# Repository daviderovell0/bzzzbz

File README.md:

**bzzzbz** is a video synthesizer that dynamically reacts to an audio input to create images and visuals that can be manipulated for integrated audio-visual performances.  <br>
This product is meant to be a simpler and cheaper alternative to commercial analog video synthesizers, still providing a flexible interface to enhance musical expression.

If you are a musician, a visual artist or are curious about the mesmerizing videos on the wall of your local techno club, build and use  **bzzzbz** to experiment and play with audio-reactive visuals! Among its main features, this open-source video synth gives you the live control of video parameters and the possibility of creating your own mappings and patterns for immersive audiovisual performances.
## Documentation
Visit our [wiki](https://github.com/daviderovell0/bzzzbz/wiki) for the full documentation. 
## Contributions
- Davide Rovelli (daviderovell0)
- Peter Nagy (deetrone)
- Marcell Illyes (marcellillyes)

This project was born at the University of Glasgow, School of Engineering. Credits to Dr.Bernd Porr, Dr. Nicholas Bailey and their Real Time Embedded Programming course.

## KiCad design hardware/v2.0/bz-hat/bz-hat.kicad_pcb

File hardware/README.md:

# Hardware
This folder contains information, documents and design files for the *bzzzbz* digital video synth hardware.

### Tools
PCBs were designed using KiCAD 5.15.

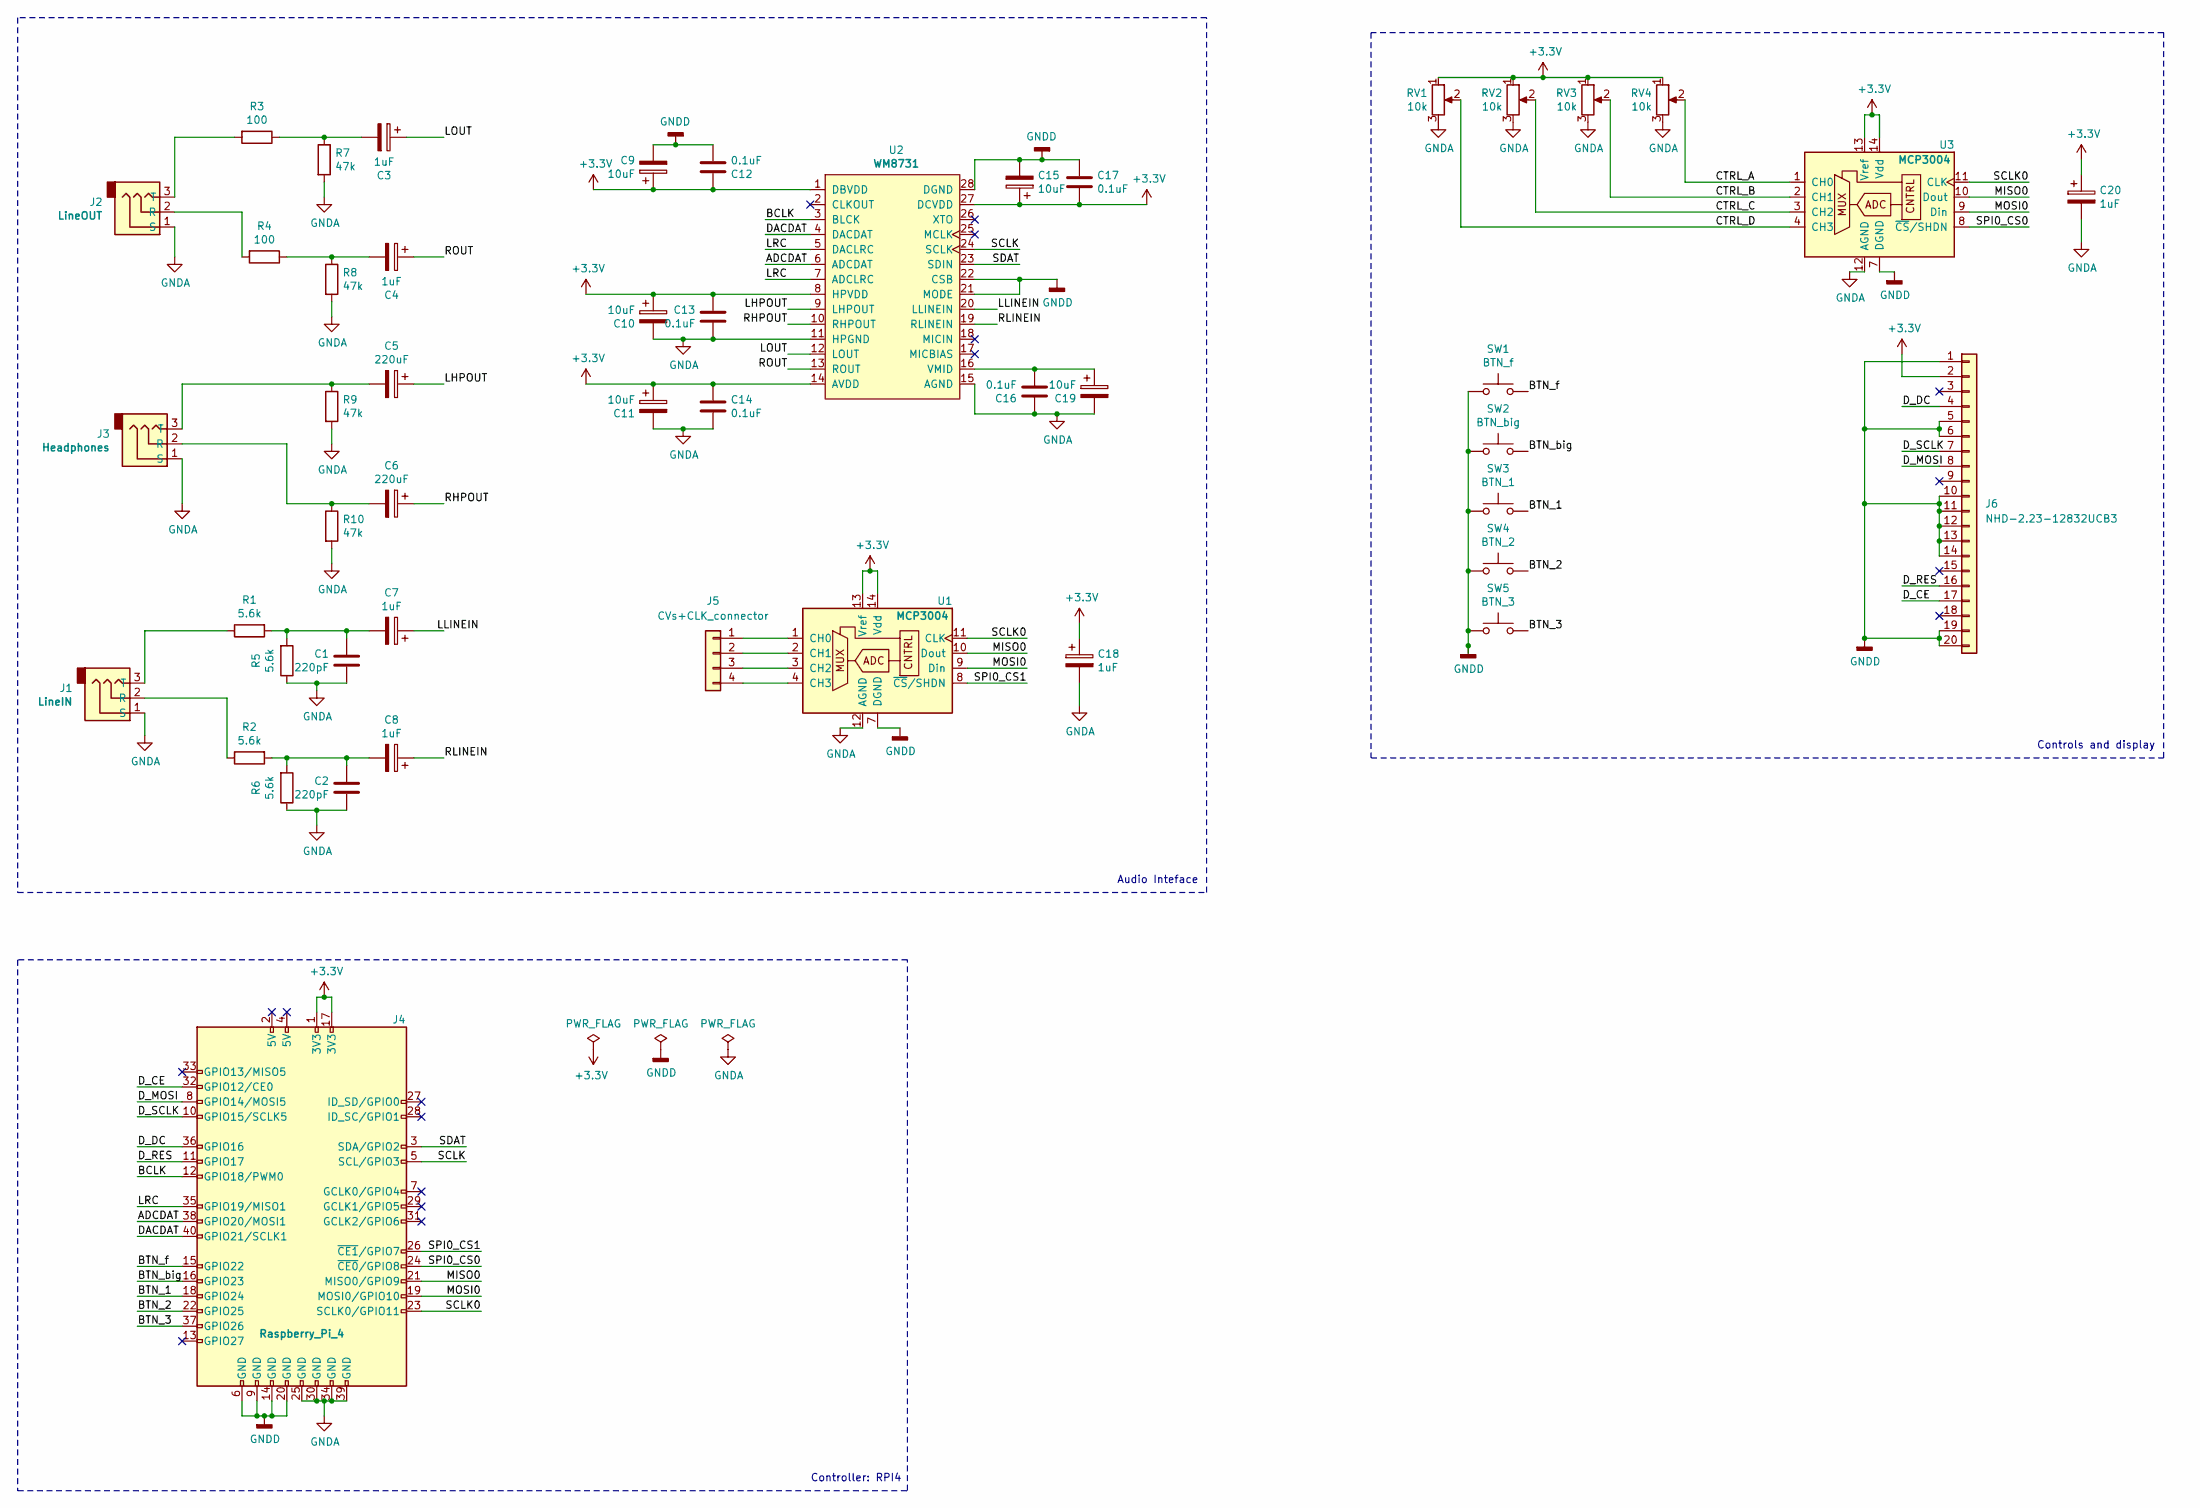
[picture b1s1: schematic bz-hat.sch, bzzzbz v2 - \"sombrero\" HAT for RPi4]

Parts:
C1, C2: 220pF; C_0603_1608Metric; Manufacturer part # CL10B221KB8NNNC; LCSC C1603
C3, C4, C7, C8, C18, C20: 1uF; CP_EIA-3216-18_Kemet-A; Manufacturer part # TAJA105K035RNJ; LCSC C7176
C5, C6: 220uF; CP_Elec_6.3x7.7; Manufacturer part # VES221M1CTR-0607; LCSC C127327
C9, C10, C11, C15, C19: 10uF; CP_EIA-3216-18_Kemet-A; Manufacturer part # TAJA106K016RNJ; LCSC C7171
C12, C14, C16, C17: 0.1uF; C_0603_1608Metric; Manufacturer part # CC0603KRX7R9BB104; LCSC C14663
C13: 0.1uF; C_1206_3216Metric; Manufacturer part # CL31B104KBCNNNC; LCSC C24497
J1: LineIN; Jack_3.5mm_CUI_SJ1-3533NG_Horizontal; Manufacturer part # SJ1-3533NG
J2: LineOUT; Jack_3.5mm_CUI_SJ1-3533NG_Horizontal; Manufacturer part # SJ1-3533NG
J3: Headphones; Jack_3.5mm_CUI_SJ1-3533NG_Horizontal; Manufacturer part # SJ1-3533NG
J4: Raspberry_Pi_4; PinHeader_2x20_P2.54mm_Vertical_RaspberryPI_HAT
J5: CVs+CLK_connector; PinHeader_1x04_P2.54mm_Vertical; Manufacturer part # 801-87-004-10-001101
J6: NHD-2.23-12832UCB3; Display_NHD-2.23-12832; Manufacturer part # NHD-2.23-12832UCB3
R1, R2, R5, R6: 5.6k; R_0805_2012Metric; Manufacturer part # 0805W8F5601T5E; LCSC C4382
R3, R4: 100; R_0805_2012Metric; Manufacturer part # 0805W8F1000T5E; LCSC C17408
R7, R8, R9, R10: 47k; R_0805_2012Metric; Manufacturer part # 0805W8F4702T5E; LCSC C17713
RV1, RV2, RV3, RV4: 10k; Potentiometer_Alps_RK09L_Single_Vertical; Manufacturer part # RK09L114001T
SW1: BTN_f; SW_PUSH-12mm+3d; Manufacturer part # TL1100F160Q6JBLK
SW2: BTN_big; SW_PUSH_e-switch_PB300_SPST_12x12; Manufacturer part # PB300STQ
SW3: BTN_1; SW_PUSH-12mm+3d; Manufacturer part # TL1100F160Q6JBLK
SW4: BTN_2; SW_PUSH-12mm+3d; Manufacturer part # TL1100F160Q6JBLK
SW5: BTN_3; SW_PUSH-12mm+3d; Manufacturer part # TL1100F160Q6JBLK
U1, U3: MCP3004; SOIC-14_3.9x8.7mm_P1.27mm; Manufacturer part # MCP3004-I/SL
U2: WM8731; SSOP28-0.65-10.2X5.2MM; Manufacturer part # WM8731SEDS/V

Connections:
+3V3: C9.1, C10.1, C11.1, C12.1, C13.1, C14.1, C15.1, C17.2, C18.1, C20.1, J4.1 (3V3), J4.17 (3V3), J6.2, RV1.1, RV2.1, RV3.1, RV4.1, U1.13 (Vref), U1.14 (Vdd), U2.1 (DBVDD), U2.8 (HPVDD), U2.14 (AVDD), U2.27 (DCVDD), U3.13 (Vref), U3.14 (Vdd)
/ADCDAT: J4.38 (GPIO20/MOSI1), U2.6 (ADCDAT)
/BCLK: J4.12 (GPIO18/PWM0), U2.3 (BLCK)
/BTN_1: J4.18 (GPIO24), SW3.2
/BTN_2: J4.22 (GPIO25), SW4.2
/BTN_3: J4.37 (GPIO26), SW5.2
/BTN_big: J4.16 (GPIO23), SW2.2
/BTN_f: J4.15 (GPIO22), SW1.2
/CTRL_A: RV4.2, U3.1 (CH0)
/CTRL_B: RV3.2, U3.2 (CH1)
/CTRL_C: RV2.2, U3.3 (CH2)
/CTRL_D: RV1.2, U3.4 (CH3)
/DACDAT: J4.40 (GPIO21/SCLK1), U2.4 (DACDAT)
/D_CE: J4.32 (GPIO12/CE0), J6.17
/D_DC: J4.36 (GPIO16), J6.4
/D_MOSI: J4.8 (GPIO14/MOSI5), J6.8
/D_RES: J4.11 (GPIO17), J6.16
/D_SCLK: J4.10 (GPIO15/SCLK5), J6.7
/LHPOUT: C5.1, U2.9 (LHPOUT)
/LLINEIN: C7.1, U2.20 (LLINEIN)
/LOUT: C3.1, U2.12 (LOUT)
/LRC: J4.35 (GPIO19/MISO1), U2.5 (DACLRC), U2.7 (ADCLRC)
/MISO0: J4.21 (MISO0/GPIO9), U1.10 (Dout), U3.10 (Dout)
/MOSI0: J4.19 (MOSI0/GPIO10), U1.9 (Din), U3.9 (Din)
/RHPOUT: C6.1, U2.10 (RHPOUT)
/RLINEIN: C8.1, U2.19 (RLINEIN)
/ROUT: C4.1, U2.13 (ROUT)
/SCLK: J4.5 (SCL/GPIO3), U2.24 (SCLK)
/SCLK0: J4.23 (SCLK0/GPIO11), U1.11 (CLK), U3.11 (CLK)
/SDAT: J4.3 (SDA/GPIO2), U2.23 (SDIN)
/SPI0_CS0: J4.24 (~CE0~/GPIO8), U3.8 (~CS~/SHDN)
/SPI0_CS1: J4.26 (~CE1~/GPIO7), U1.8 (~CS~/SHDN)
GNDA: C1.2, C2.2, C10.2, C11.2, C13.2, C14.2, C16.1, C18.2, C19.2, C20.2, J1.1 (S), J2.1 (S), J3.1 (S), J4.25 (GND), J4.30 (GND), J4.34 (GND), J4.39 (GND), R5.1, R6.1, R7.2, R8.2, R9.2, R10.2, RV1.3, RV2.3, RV3.3, RV4.3, U1.12 (AGND), U2.11 (HPGND), U2.15 (AGND), U3.12 (AGND)
GNDD: C9.2, C12.2, C15.2, C17.1, J4.6 (GND), J4.9 (GND), J4.14 (GND), J4.20 (GND), J6.1, J6.5, J6.6, J6.10, J6.11, J6.12, J6.13, J6.14, J6.19, J6.20, SW1.1, SW2.1, SW3.1, SW4.1, SW5.1, U1.7 (DGND), U2.21 (MODE), U2.22 (CSB), U2.28 (DGND), U3.7 (DGND)
unnamed: C1.1, C7.2, R1.2, R5.2
unnamed: C2.1, C8.2, R2.2, R6.2
unnamed: C3.2, R3.1, R7.1
unnamed: C4.2, R4.1, R8.1
unnamed: C5.2, J3.3 (T), R9.1
unnamed: C6.2, J3.2 (R), R10.1
unnamed: C16.2, C19.1, U2.16 (VMID)
unnamed: J1.2 (R), R2.1
unnamed: J1.3 (T), R1.1
unnamed: J2.2 (R), R4.2
unnamed: J2.3 (T), R3.2
unnamed: J5.1, U1.1 (CH0)
unnamed: J5.2, U1.2 (CH1)
unnamed: J5.3, U1.3 (CH2)
unnamed: J5.4, U1.4 (CH3)

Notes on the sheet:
Audio Inteface
Controls and display
Controller: RPI4

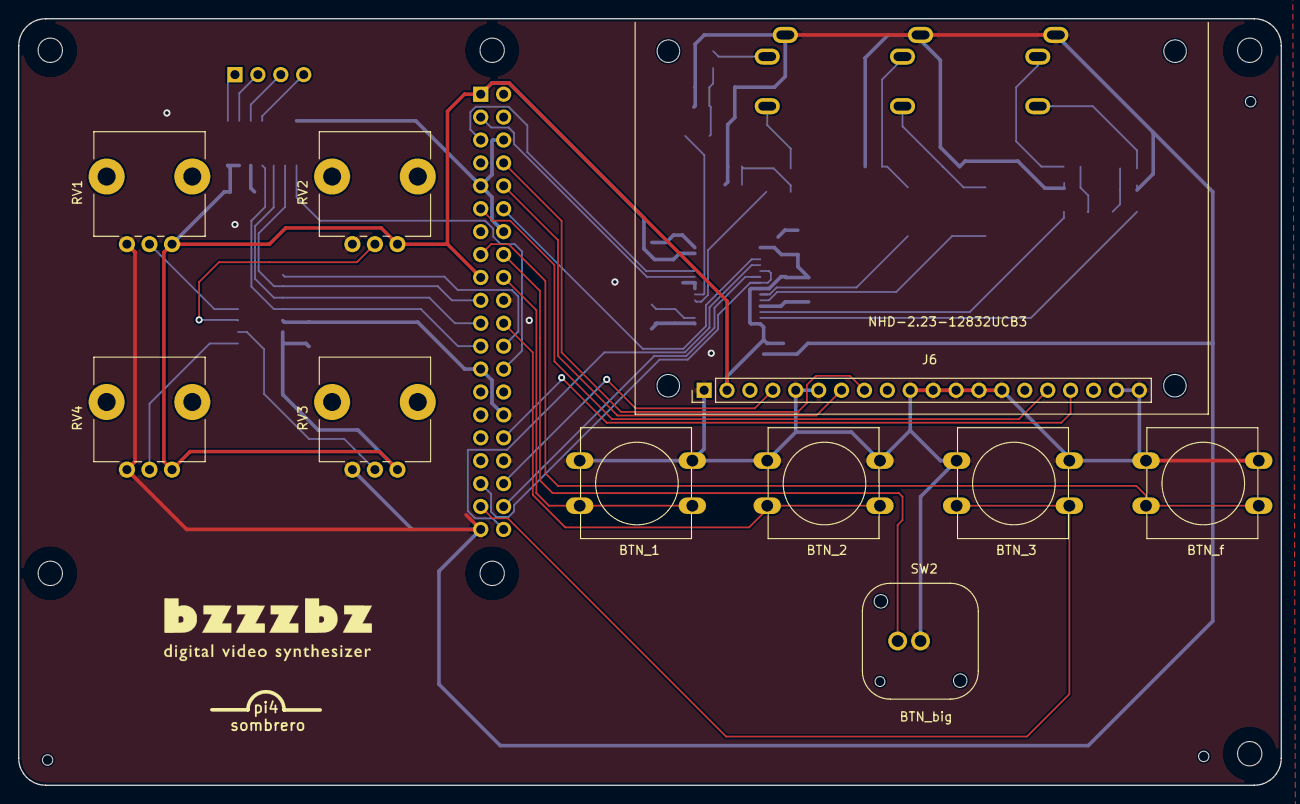
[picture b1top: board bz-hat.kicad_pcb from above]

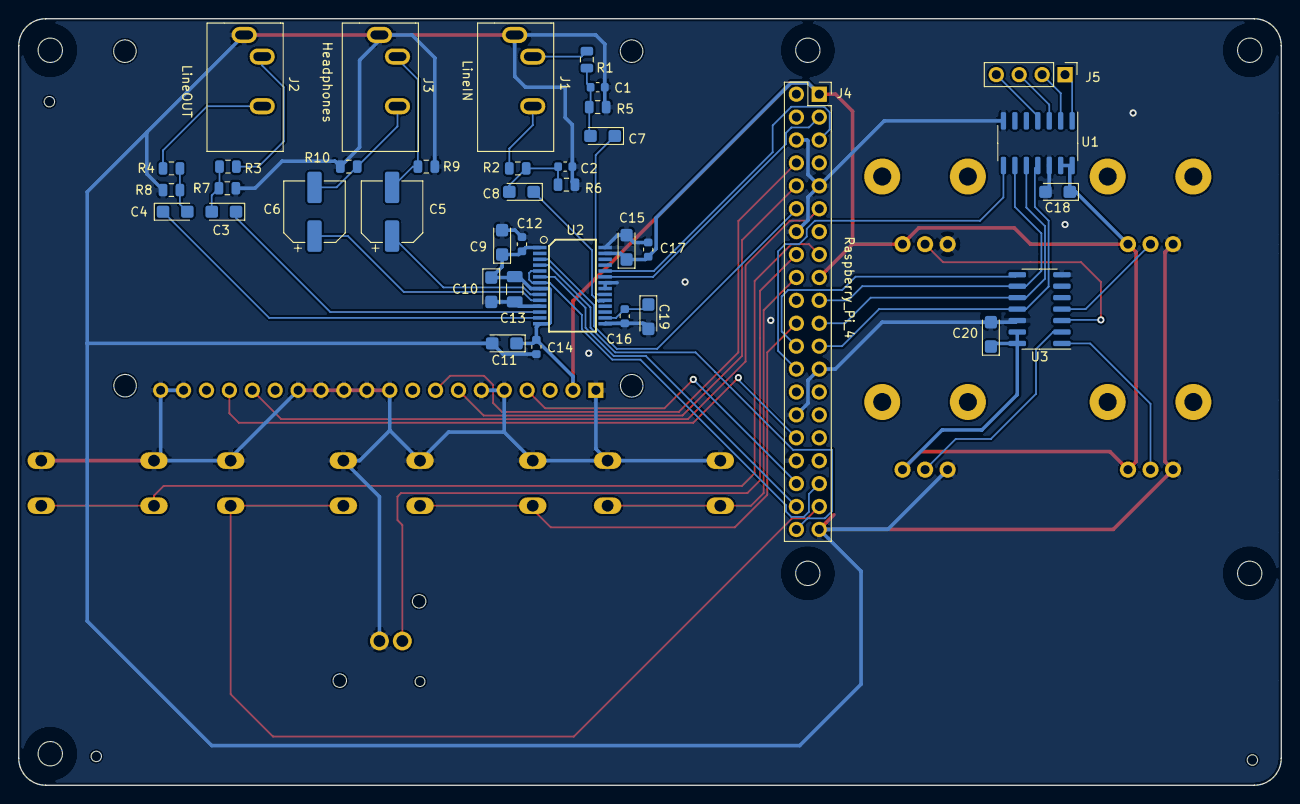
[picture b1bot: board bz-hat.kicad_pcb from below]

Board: 2 copper layers, 140.0 x 85.0 mm, 48 parts (38 on the bottom side), 49 nets.

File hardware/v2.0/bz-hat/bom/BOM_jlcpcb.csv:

Comment,Designator,Footprint,LCSC
220pF,"C1,C2",Capacitor_SMD:C_0603_1608Metric,C1603
0.1uF,C13,Capacitor_SMD:C_1206_3216Metric,C24497
10uF,"C9,C10,C11,C15,C19",Capacitor_Tantalum_SMD:CP_EIA-3216-18_Kemet-A,C7171
0.1uF,"C12,C14,C16,C17",Capacitor_SMD:C_0603_1608Metric,C14663
220uF,"C5,C6",Capacitor_SMD:CP_Elec_6.3x7.7,C127327
1uF,"C3,C4,C7,C8,C18,C20",Capacitor_Tantalum_SMD:CP_EIA-3216-18_Kemet-A,C7176
LineIN,J1,custom:Jack_3.5mm_CUI_SJ1-3533NG_Horizontal,
LineOUT,J2,custom:Jack_3.5mm_CUI_SJ1-3533NG_Horizontal,
Headphones,J3,custom:Jack_3.5mm_CUI_SJ1-3533NG_Horizontal,
Raspberry_Pi_4,J4,custom:PinHeader_2x20_P2.54mm_Vertical_RaspberryPI_HAT,
CVs+CLK_connector,J5,Connector_PinHeader_2.54mm:PinHeader_1x04_P2.54mm_Vertical,
NHD-2.23-12832UCB3,J6,custom:Display_NHD-2.23-12832,
5.6k,"R1,R2,R5,R6",Resistor_SMD:R_0805_2012Metric,C4382
100,"R3,R4",Resistor_SMD:R_0805_2012Metric,C17408
47k,"R7,R8,R9,R10",Resistor_SMD:R_0805_2012Metric,C17713
10k,"RV1,RV2,RV3,RV4",Potentiometer_THT:Potentiometer_Alps_RK09L_Single_Vertical,
BTN_f,SW1,custom:SW_PUSH-12mm+3d,
BTN_big,SW2,custom:SW_PUSH_e-switch_PB300_SPST_12x12,
BTN_1,SW3,custom:SW_PUSH-12mm+3d,
BTN_2,SW4,custom:SW_PUSH-12mm+3d,
BTN_3,SW5,custom:SW_PUSH-12mm+3d,
MCP3004,"U1,U3",Package_SO:SOIC-14_3.9x8.7mm_P1.27mm,C512186
WM8731,U2,custom:SSOP28-0.65-10.2X5.2MM,C323837

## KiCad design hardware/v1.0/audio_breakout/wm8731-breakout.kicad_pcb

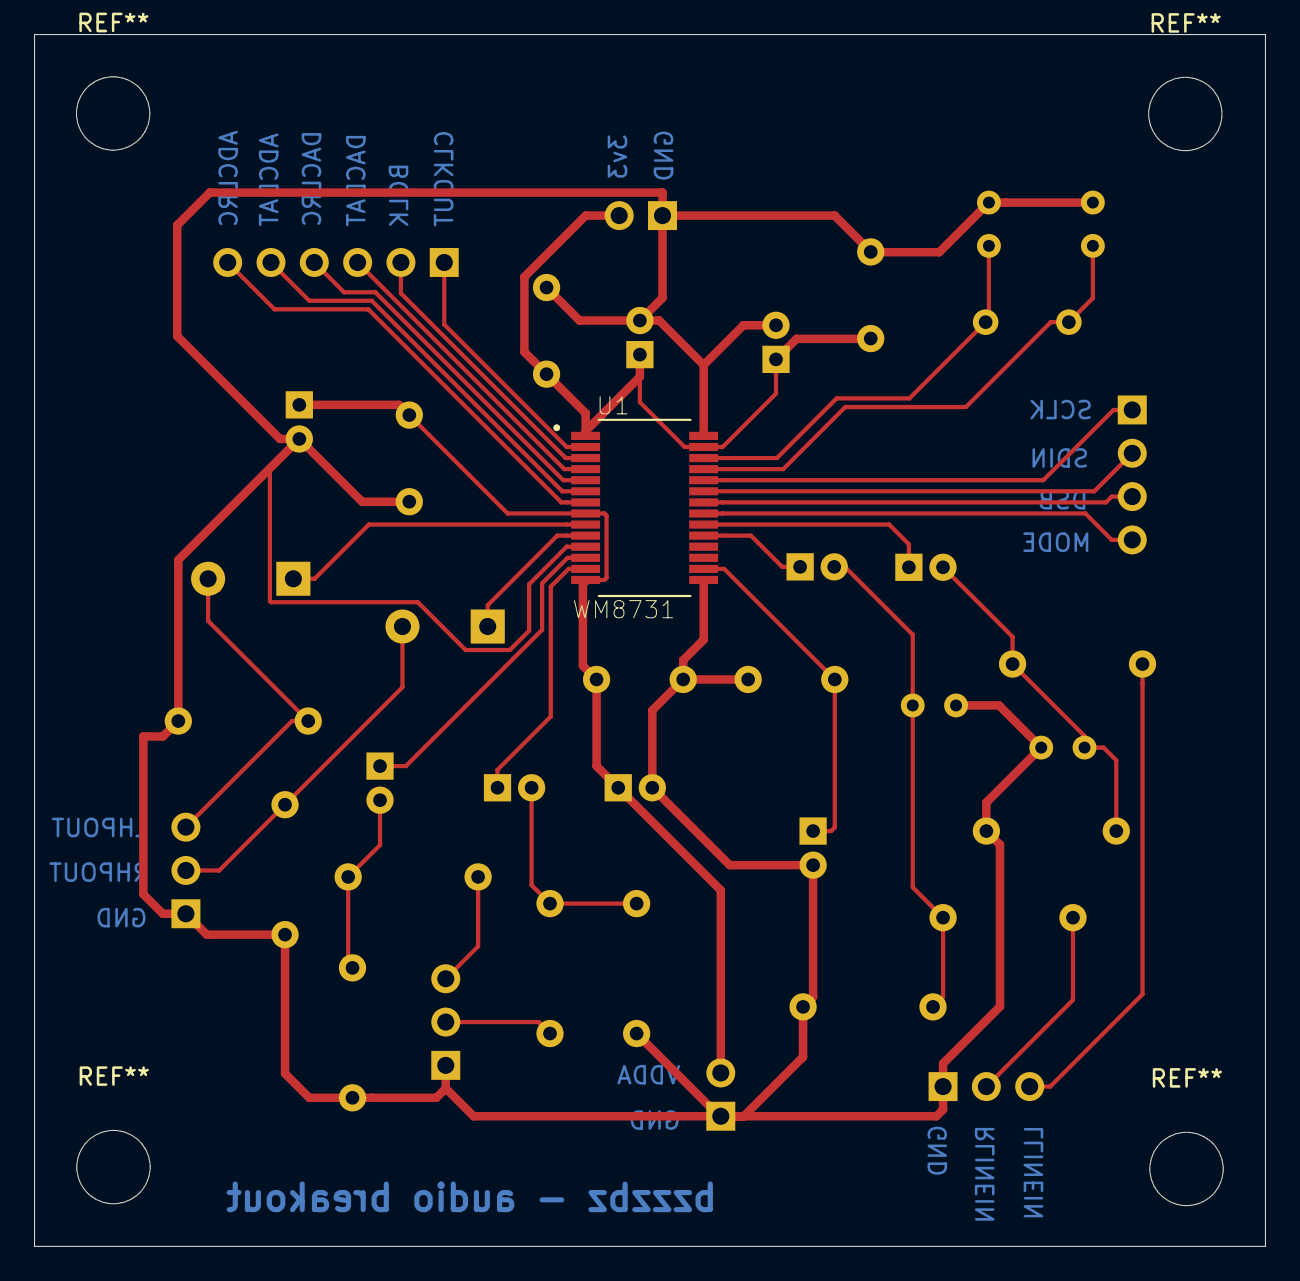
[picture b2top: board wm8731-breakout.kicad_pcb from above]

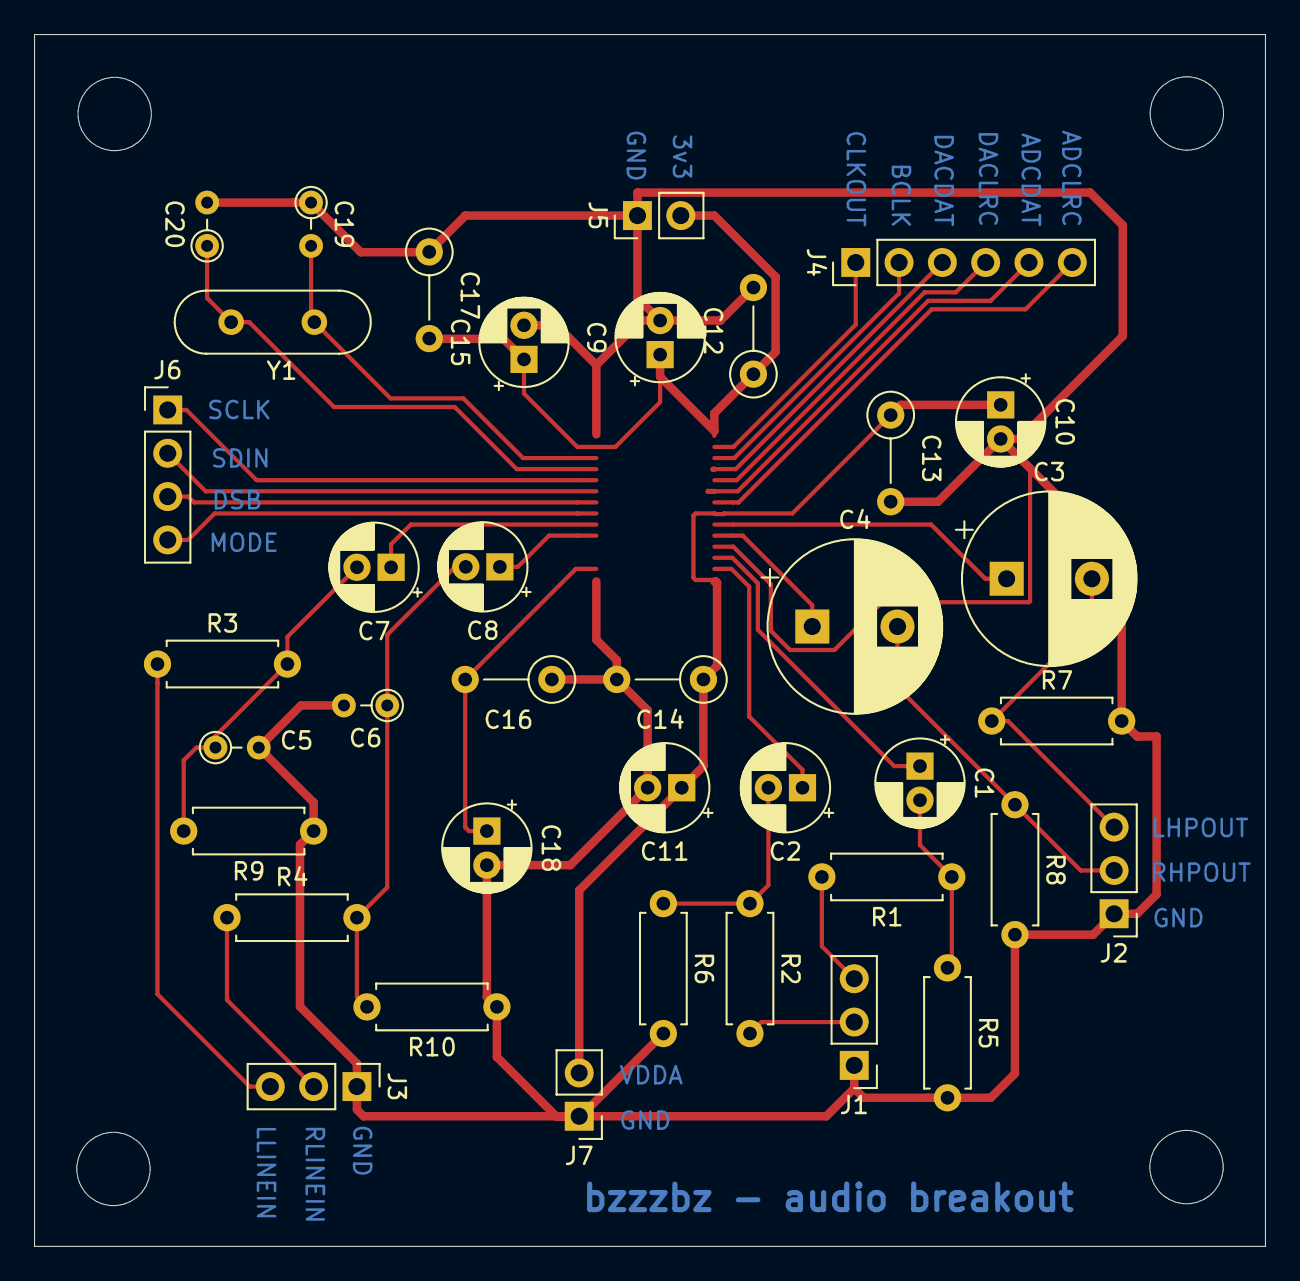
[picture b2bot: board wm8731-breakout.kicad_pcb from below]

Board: 2 copper layers, 72.2 x 71.1 mm, 39 parts (38 on the bottom side), 32 nets.

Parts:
C1, C2, C7, C8: 1uF; CP_Radial_D5.0mm_P2.00mm
C3, C4: 220uF; CP_Radial_D10.0mm_P5.00mm
C5, C6: 220pF; R_Axial_DIN0204_L3.6mm_D1.6mm_P2.54mm_Vertical
C9, C10, C11, C15, C18: 10uF; CP_Radial_D5.0mm_P2.00mm
C12, C13, C14, C16, C17: 0.1uF; R_Axial_DIN0207_L6.3mm_D2.5mm_P5.08mm_Vertical
C19, C20: 22pF; R_Axial_DIN0204_L3.6mm_D1.6mm_P2.54mm_Vertical
J1: LineOUT; PinHeader_1x03_P2.54mm_Vertical
J2: Headphones; PinHeader_1x03_P2.54mm_Vertical
J3: LineIN; PinHeader_1x03_P2.54mm_Vertical
J4: Conn_01x06; PinHeader_1x06_P2.54mm_Vertical
J5: Conn_01x02_3v3 (2); PinHeader_1x02_P2.54mm_Vertical
J6: Conn_01x04; PinHeader_1x04_P2.54mm_Vertical
J7: Conn_01x02_3v3 (1); PinHeader_1x02_P2.54mm_Vertical
R1, R2: 100; R_Axial_DIN0207_L6.3mm_D2.5mm_P7.62mm_Horizontal
R3, R4, R9, R10: 5.6k; R_Axial_DIN0207_L6.3mm_D2.5mm_P7.62mm_Horizontal
R5, R6, R7, R8: 47k; R_Axial_DIN0207_L6.3mm_D2.5mm_P7.62mm_Horizontal
U1: WM8731; SOP65P777X199-28N
Y1: Crystal - 12 MHz; Crystal_2pins_L11.5_P4.88_(9B-12.000MAAJ-B)

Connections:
/LHPOUT: C3.1, U1.9
/LLINEIN: C7.1, U1.20
/LOUT: C1.1, U1.12
/RHPOUT: C4.1, U1.10
/RLINEIN: C8.1, U1.19
/ROUT: C2.1, U1.13
GND: C5.2, C6.2, C9.2, C10.2, C11.2, C12.2, C13.2, C14.2, C15.2, C16.1, C17.1, C18.2, C19.1, C20.2, J1.1, J2.1, J3.1, J5.1, J7.1, R5.2, R6.2, R7.2, R8.2, R9.1, R10.1, U1.11, U1.15, U1.28
unnamed: C1.2, R1.1, R5.1
unnamed: C2.2, R2.1, R6.1
unnamed: C3.2, J2.3, R7.1
unnamed: C4.2, J2.2, R8.1
unnamed: C5.1, C7.2, R3.2, R9.2
unnamed: C6.1, C8.2, R4.2, R10.2
unnamed: C16.2, C18.1, U1.16
unnamed: C19.2, U1.26, Y1.1
unnamed: C20.1, U1.25, Y1.2
unnamed: J1.2, R2.2
unnamed: J1.3, R1.2
unnamed: J3.2, R4.1
unnamed: J3.3, R3.1
unnamed: J4.1, U1.2
unnamed: J4.2, U1.3
unnamed: J4.3, U1.4
unnamed: J4.4, U1.5
unnamed: J4.5, U1.6
unnamed: J4.6, U1.7
unnamed: J6.1, U1.24
unnamed: J6.2, U1.23
unnamed: J6.3, U1.22
unnamed: J6.4, U1.21
VDD: C9.1, C12.1, C15.1, C17.2, J5.2, U1.1, U1.27
VDDA: C10.1, C11.1, C13.1, C14.1, J7.2, U1.8, U1.14

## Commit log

2020-01-23 commiting now
2020-01-23 test commit
2020-01-23 Main audio test
2020-01-23 Video Processing test
2020-01-23 gitignore (exe) added
2020-01-23 gitignore .out added
2020-01-28 README - Initial description
2020-02-20 Added first OpenGL code, displays triangle
2020-02-25 Color (multi) triangle
2020-03-02 Breakout PCB v1
2020-03-05 Dependiecies section on README
2020-03-10 video of changing triangle
2020-03-24 Added schematic PDF
2020-03-24 folder names to lowercase
2020-03-24 Duplicate folder error
2020-03-24 Restoring triangle video
2020-03-25 Jack client + simple deploy script
2020-03-25 Makefile for audio and temp cmakelists
2020-03-27 Makefile for ubuntu local dev
2020-03-28 Mic in basic JACK program
2020-03-28 Sample audio data + simple py plotter
2020-03-30 Pi sample data
2020-03-31 kiss_fft for sample data init
2020-03-31 Simple potentiometer program
    SPI classes to read in the potentiometer values
2020-03-31 Multichannel polling stream
2020-04-01 kissFFT test and plot on sample data
2020-04-02 FFT magnitude computation
2020-04-03 Draft AudioProcessing class (BUG)
2020-04-04 Bug fixed. Working incoming audio within cpp class
2020-04-04 rolling FFT with audio. NON-threaded
2020-04-06 Added kiss-fft source for portability
2020-04-06 Rolling FFT test data
2020-04-07 Integration: audio varying simple openGL triagle
2020-04-07 Cmake + added control files
2020-04-08 Created GPL license
2020-04-08 new_shader_windowing
2020-04-09 kiss-fft into submodule linked to official repo
2020-04-09 Set theme jekyll-theme-cayman
2020-04-09 Set theme jekyll-theme-minimal
2020-04-09 window.cpp implemented in main.cpp, shaders updated
2020-04-09 updated opengl and glsl code
2020-04-09 Included control for potentiometers over SPI
2020-04-11 Made the bass bin (0,750Hz] of the FFT_frame a dynamic variable in OpenGL
2020-04-11 fft_frame index corrected
2020-04-14 deleted old makefile
2020-04-14 Added EQ shader and modified main accordingly(binding array)
2020-04-14 type change for glsl compatibility
2020-04-14 temp change for audio demo
2020-04-14 increased buffer size to (try) to avoid xrun
2020-04-14 Fixed FFT bug. Working eq on laptop with nfft 1024
2020-04-14 removed object file
2020-04-14 changes to window.cpp and comments updated
2020-04-14 added opengl related dependencies
2020-04-15 removed kissfft as submodule to ease modifications
2020-04-15 new audio processing routine
2020-04-15 Improved Makefile for video_processing sample shader
2020-04-16 Dependencies script for raspberry pi
2020-04-16 fixed dependencies scirpt
2020-04-16 EQ speed improvement, fully RT reactive
2020-04-18 updated cells.glsl and main.cpp, small change to dependencies.sh
2020-04-18 Clean-up repository and main folder restructure
2020-04-18 Added media folder
2020-04-18 Moved audio_processing into src
2020-04-18 Added hardware files for control + relative medias
2020-04-18 Restored cmake file for spi_test
2020-04-18 createddemos for all parts, updated shaders
2020-04-18 created examples for to demo opengl, spi and audio (fft)
2020-04-18 Added cmake for examples
2020-04-19 Updated README and added images
2020-04-19 Remove title
2020-04-19 update to documentation
2020-04-19 Added hardware last pictures
2020-04-19 added Doxygen documentation
2020-04-19 Doxygen docs redirect for guthub pages
2020-04-19 Added the TestLatency class and initialized in main Can be used for measuring the time delay between acquiring audio data and swapping buffers upon render in GLUT with an oscilloscope
2020-04-19 Added Unit tests to repo
2020-04-19 Added TestLatency in linking
2020-04-19 gitignore to avoid including cmake related files in the repository
2020-04-19 Compact Cmake structure with subdirs and tests
2020-04-19 Testing latency between audio transient at bin 5 and video render
2020-04-19 testing routine commit
2020-04-20 update main.cpp and cells.glsl to fixed values, disabled ap and m
2020-04-20 edited main for audio+control graphics
2020-04-20 Updated dependencies with BOOST
2020-04-20 AudioProcessing test suite imported to github
2020-04-20 MCP3008Comm unit test + refactoring
2020-04-20 Complete unit tests, folder restructure info added
2020-04-20 Doxygen updated docs
2020-04-20 Copy to merge with master
2020-04-20 Add files via upload
    Added files for tests
2020-04-20 deleted not-working functions and cleared up code
2020-04-20 finished doc of main.cpp, update doxygen
2020-04-20 finished doxygen
2020-04-20 software diagram
2020-04-20 software diagram added
2020-04-30 added build-essential and cmake to dependencies.sh
2020-04-30 deleted bz exec
2021-02-22 board v2 init and folder restructure
2021-02-22 KiCAD - raspberrypi 4 symbol and MCP3004s added
2021-02-24 v2 schematic full draft
2021-02-27 Fixed ERC. Full v2 sombrero schematic
2021-03-02 big button (PB300) footprint
2021-03-06 Fixed footprints and added 3d models
2021-03-07 v2 board, mounting holes + draft components placement
2021-03-09 v2 board placement and routing finished
2021-03-25 logo + gerbers + JLPCB refs. to symbols
2021-03-26 added BOM and pick and place file
2021-03-30 Fixed C19 wrong footprint
2021-03-30 Updated gerbers + BOM + centroid files for JLCPCB
2021-04-11 Added interactive BOM with manufacturer, distributor, price fields
2021-04-21 Full BOM with pricing uploaded, male header and SD missing
2021-05-09 MCP3004 implementation + updated spi test for brd v2
2021-05-25 added last components in BOM for prices reference
2021-05-25 pictures of board v2 assembled and mounted
2021-12-28 removing jupyter checkpoints
2021-12-28 added 3d render of pots
2022-01-07 symbols update and rm jupyter checkpoints
2022-01-07 working display test: screen lit on via SPI + init classes
2023-06-11 display and GPIO chardev skeleton classes
2023-06-11 display init classes update
